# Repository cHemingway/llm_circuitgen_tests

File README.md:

# llm_circuitgen_tests

A benchmark of "circuit as code" tools for LLM-aided circuit design. Every tool
gets the same design brief, and each implementation lives in its own top-level
folder.

Model is Claude Opus 5.5 on Extra thinking level

## Brief

This repository is a benchmark of various "circuit as code" tools for LLM-aided
circuit design. Each tool is given the same prompt, with the tool name and branch
substituted where needed:

> Use `<tool>` to design me a RP2354A powered Solartron 7075 multimeter
> interface, using the 50 way D connector on the Solartron. Put it in the folder
> `<tool>`. Do these changes on a new branch.
>
> DO NOT LOOK AT OTHER BRANCHES FOR CODE, RELY ON THE TOOL, THE DATASHEET, AND
> WHAT YOU CAN FIND ONLINE ONLY, DON'T COPY THE OUTPUTS OF OTHER TOOLS USED IN
> THIS BENCHMARK.
>
> In the top level folder `inputs` is a datasheet for the multimeter. It
> describes how the interface works in section 9.
>
> Signals to/from the multimeter should be opto-isolated to prevent USB ground
> noise from affecting the system. I was thinking therefore they should be done
> through shift registers to minimise the number of signals across the isolation
> barrier.
>
> Select parts from `<tool>`'s library, then LCSC where possible.
>
> Have the board sit flat on the back of the multimeter, using a vertical PCB
> mount D-Sub connector on one side and a vertical USB-B connector on the other
> side of the board.
>
> The board will be rectangular, and mechanically fixed to the solartron using
> the jackscrews on the D-Sub connector, so doesn't need any other mounting
> holes.

When the design work is finished, the session is asked to export the
conversation and add its figures to the Results and Breakdown tables below,
using the prompt in [`EXPORT_PROMPT.md`](EXPORT_PROMPT.md).

## Results

| Tool | Folder | Active time | of which tool time | Total tokens | API calls | API-price estimate | Schematic | PCB prints | Notes |
| --- | --- | --- | --- | --- | --- | --- | --- | --- | --- |
| [tscircuit](https://tscircuit.com) | `tscircuit/` | 3 h 11 min | 2 h 06 min | 156.3 M | 376 | $59.32 | [PDF](tscircuit/outputs/schematic.pdf) | [PDF](tscircuit/outputs/pcb-prints.pdf) | Parts from tscircuit/common, then LCSC. Session log and statistics: [`tscircuit/CONVERSATION.md`](tscircuit/CONVERSATION.md) |
| [atopile](https://atopile.io) | `atopile/` | 1 h 46 min | 38 min | 149.5 M | 370 | $49.34 | [PDF](atopile/schematic/solartron_7075_usb.pdf) | [PDF](atopile/fab/solartron_7075_usb_prints.pdf) | CLI version (`ato`, 0.15.x). This is the last open CLI line and is effectively end-of-life: [PyPI](https://pypi.org/project/atopile/) lists 0.15.9 (12 Sep 2026) as the latest release, and atopile has moved on to [0.16](https://atopile.io/enterprise). Parts from atopile's library, then LCSC. Session log and statistics: [`atopile/CONVERSATION.md`](atopile/CONVERSATION.md) |
| [SKiDL](https://github.com/devbisme/skidl) | `skidl/` | 2 h 29 min | 59 min | 124.5 M | 347 | $46.64 | [PDF](skidl/pcb/render/schematic.pdf) | [PDF](skidl/pcb/print/pcb_prints.pdf) | SKiDL 2.3.0 on KiCad 10 (the brief added "use KiCad 10"). SKiDL has no part library of its own, so parts come from KiCad's libraries, then LCSC. Board built with kinet2pcb and routed with Freerouting 2.5. SKiDL's schematic generator mis-connects nets on this design, so the schematic is drawn by a script and checked against the netlist. Statistics run to the conversation export, and exclude the merge into `main` that came after it. Session log and statistics: [`skidl/CONVERSATION.md`](skidl/CONVERSATION.md) |
| [Manta](https://github.com/Derrick-Derrickson/Manta) | `manta/` | 46 min | – | 62.9 M | 191 | – | [HTML](manta/output/solartron7075.html) | – | Manta 2.0.1 (language revision 2.0). Manta is a schematic and netlist language with no layout, so the result is a checked netlist, a KiCad netlist (with a footprint map and two generated footprints), an LCSC BOM and an HTML schematic. No PCB was made, so there are no prints. Manta's only part library is its `blinky` example; 8 part types came from it, the rest from LCSC. The session transcript kept no cost-state record, so tool time and the price estimate were not recorded; tokens and API calls are summed from the transcript's per-response usage. Statistics run to the conversation export, and exclude the merge into `main` that came after it. Notes on the tool: [`manta/README.md`](manta/README.md#notes-on-the-tool-benchmark-observations). Session log and statistics: [`manta/CONVERSATION.md`](manta/CONVERSATION.md) |
| [Konnect](https://github.com/mixelpixx/Konnect) | `konnect/` | 3 h 33 min | 56 min | 264.4 M | 520 | $112.18 | [PDF](konnect/fab/schematic.pdf) | [PDF](konnect/fab/pcb_layers.pdf) | Konnect 0.13.0, an MCP server that drives KiCad 10.0.6. Parts come from KiCad's libraries, with LCSC numbers. KiCad has no DD-50, so its symbol and footprint were made in the project library. Konnect's Freerouting export refuses KiCad's roundrect pads, so the SMD footprints were copied with rectangular pads. The board was routed with Freerouting 2.4.1 after a pad-rotation bug in Konnect's DSN export was fixed by hand. The ground pours needed hand-placed stitching vias and a small grid router written in the scratchpad. The run stopped twice at a usage limit (12 h 53 min in all, left out of active time) and was compacted once. Tool time and the price estimate are the tool's own counters. The Breakdown prices use the published Opus 5.5 and Haiku 5.5 prices, which reproduce those counters. Statistics run to the conversation export, and exclude the merge into `main` that came after it. Notes on the tool: [`konnect/README.md`](konnect/README.md#notes-on-the-tool). Session log and statistics: [`konnect/CONVERSATION.md`](konnect/CONVERSATION.md) |
| [Fable 5.2 + KiCad](https://www.kicad.org) | `fable_5.2/` | 1 h 18 min | 18 min | 43.9 M | 122 | $46.05 | [PDF](fable_5.2/docs/schematic.pdf) | [PDF](fable_5.2/docs/pcb_top.pdf) | KiCad 10.0.8 (PPA), driven through `kicad-cli` and the `pcbnew` Python module with scripts that write the schematic and board files. Parts come from KiCad's libraries, then LCSC numbers checked against the JLCPCB catalogue. KiCad has no DD-50 plug or TPIC6C595, so those two symbols and the DD-50 and DC-DC footprints were made in the project library. Freerouting could not be run here (executing the downloaded jar was blocked), so the 4-layer board was routed with a grid router written in the project; it has no DRC errors or unconnected pads. The run stopped twice at a usage limit (9 h 06 min in all, left out of active time) and the context was not compacted within the span. Tool time and the price estimate are the tool's own counters. The Breakdown prices use the published per-token prices of the session model, which reproduce those counters. Statistics run to the conversation export, and exclude the merge into `main` that came after it. Notes on the run: [`fable_5.2/README.md`](fable_5.2/README.md#session-statistics). Session log and statistics: [`fable_5.2/CONVERSATION.md`](fable_5.2/CONVERSATION.md) |

Statistics cover the Claude Code session from the first prompt to the merge into
`main`.

- **Active time:** Claude working, including tool runs such as autorouting. It
  excludes time spent waiting for the user.
- **Of which tool time:** the part of the active time spent running tools
  (builds, exports, autorouting, searches) rather than in model calls.
- **Total tokens:** these include prompt-cache reads, which dominate the total
  because every API call re-sends the conversation.
- **API-price estimate:** Claude Code's estimate at API list prices, not a bill.

A dash means the figure was not recorded.

## Breakdown

The Results figures for each tool, split by the kind of work. Every API call in
the session is put in one category according to what it was doing:

- **Schematic & research:** reading the manual, choosing parts and looking them
  up, datasheets and tool documentation, writing the circuit, and netlist and
  schematic work.
- **PCB:** footprints, placement, routing, DRC and other board checks, Gerbers,
  fabrication fixes and PCB prints.
- **Other:** commits, pushes, README writing, status checks and final
  summaries.
- **Not attributable:** calls the session's counters include but the transcript
  doesn't log, such as the `/compact` summary.

How the figures are measured:

- **Tokens:** summed from each call's logged usage.
- **Active time:** each call is credited with the time until the next call,
  including the tool runs it started.
- **API-price estimate:** per-token prices fitted to the session's cost counter
  are applied to each category's tokens.

Calls that did both kinds of work are assigned by their main purpose.

### tscircuit

| | Schematic & research | PCB | Other | Not attributable | Total |
| --- | --- | --- | --- | --- | --- |
| Active time | 1 h 08 min | 1 h 57 min | 4 min | 1 min | 3 h 11 min |
| API calls | 171 | 174 | 31 | – | 376 |
| Total tokens | 61.6 M | 75.2 M | 16.0 M | 3.5 M | 156.3 M |
| Tokens excl. cache reads | 1.33 M | 0.57 M | 0.74 M | 0.74 M | 3.38 M |
| Output tokens | 169 k | 178 k | 26 k | 9 k | 382 k |
| API-price estimate | $24.69 | $21.64 | $9.32 | $3.67 | $59.32 |

### atopile

| | Schematic & research | PCB | Other | Not attributable | Total |
| --- | --- | --- | --- | --- | --- |
| Active time | 1 h 06 min | 31 min | 9 min | 0 min | 1 h 46 min |
| API calls | 226 | 87 | 57 | – | 370 |
| Total tokens | 78.2 M | 42.0 M | 24.7 M | 4.6 M | 149.5 M |
| Tokens excl. cache reads | 0.75 M | 0.32 M | 0.80 M | 0.09 M | 1.97 M |
| Output tokens | 217 k | 104 k | 42 k | 16 k | 378 k |
| API-price estimate | $24.10 | $12.17 | $11.70 | $1.37 | $49.34 |

### SKiDL

| | Schematic & research | PCB | Other | Not attributable | Total |
| --- | --- | --- | --- | --- | --- |
| Active time | 1 h 06 min | 1 h 17 min | 5 min | 1 min | 2 h 29 min |
| API calls | 165 | 158 | 24 | – | 347 |
| Total tokens | 53.3 M | 61.0 M | 9.0 M | 1.1 M | 124.5 M |
| Tokens excl. cache reads | 0.74 M | 0.62 M | 0.69 M | 0.01 M | 2.07 M |
| Output tokens | 238 k | 196 k | 27 k | 9 k | 470 k |
| API-price estimate | $19.31 | $19.39 | $7.51 | $0.43 | $46.64 |

### Konnect

| | Schematic & research | PCB | Other | Not attributable | Total |
| --- | --- | --- | --- | --- | --- |
| Active time | 45 min | 2 h 45 min | 2 min | 1 min | 3 h 33 min |
| API calls | 147 | 364 | 9 | – | 520 |
| Total tokens | 54.5 M | 197.5 M | 7.3 M | 5.1 M | 264.4 M |
| Tokens excl. cache reads | 0.83 M | 3.78 M | 0.84 M | 1.06 M | 6.51 M |
| Output tokens | 235 k | 552 k | 6 k | 17 k | 810 k |
| API-price estimate | $20.17 | $75.58 | $8.12 | $8.32 | $112.18 |

### Fable 5.2 + KiCad

| | Schematic & research | PCB | Other | Not attributable | Total |
| --- | --- | --- | --- | --- | --- |
| Active time | 38 min | 38 min | 2 min | 0 min | 1 h 18 min |
| API calls | 67 | 48 | 7 | – | 122 |
| Total tokens | 16.5 M | 23.5 M | 3.9 M | 0 | 43.9 M |
| Tokens excl. cache reads | 0.54 M | 0.33 M | 0.96 M | 0 | 1.82 M |
| Output tokens | 198 k | 145 k | 9 k | 0 | 352 k |
| API-price estimate | $16.63 | $13.32 | $16.09 | $0.00 | $46.05 |

## Review feedback

After the design is finished, each tool's session gets the same review comments,
in this order:

> 1. Can you tidy up the routing through pin swapping the shift registers /
>    resistor arrays?
> 2. Did you try swapping pins between parts as well or just within the same
>    part?
> 3. Try moving parts too

Statistics are measured as above, from the first review comment to the last
reply.

When the review is finished, the session is asked to export the review log and
fill in its row below, using the prompt in
[`REVIEW_EXPORT_PROMPT.md`](REVIEW_EXPORT_PROMPT.md).

| Tool | Active time | of which tool time | Total tokens | API calls | API-price estimate | Notes |
| --- | --- | --- | --- | --- | --- | --- |
| [tscircuit](https://tscircuit.com) | 1 h 35 min | 1 h 12 min | 48.9 M | 97 | $16.38 | Review log and statistics: [`tscircuit/REVIEW_CONVERSATION.md`](tscircuit/REVIEW_CONVERSATION.md) |
| [atopile](https://atopile.io) | 2 h 28 min | 2 h 03 min | 53.1 M | 141 | $16.94 | Review log and statistics: [`atopile/REVIEW_CONVERSATION.md`](atopile/REVIEW_CONVERSATION.md) |
| [SKiDL](https://github.com/devbisme/skidl) | 38 min | 21 min | 34.1 M | 65 | $9.80 | Turn 1 from Claude Code's counters. No counter record was written after turns 2–3, so their tokens come from the transcript, their tool time from tool-call timestamps and their price from per-token prices fitted to the session's cost snapshots. Review log and statistics: [`skidl/REVIEW_CONVERSATION.md`](skidl/REVIEW_CONVERSATION.md) |
| [Manta](https://github.com/Derrick-Derrickson/Manta) | – | – | – | – | – | |
| [Konnect](https://github.com/mixelpixx/Konnect) | 2 h 35 min | 49 min | 226.6 M | 413 | $86.47 | The resumed session wrote no cost-state counters, so every figure comes from the transcript. Tokens and API calls are summed from the per-response usage. Tool time is each tool call's request-to-result time, which reads about 4 % high. The price uses the published Opus 5.5 prices. Active time leaves out a 26 min wait for the user's answer, two usage-limit stops, and about an hour when the API could not be reached. Review log and statistics: [`konnect/REVIEW_CONVERSATION.md`](konnect/REVIEW_CONVERSATION.md) |
| [Fable 5.2 + KiCad](https://www.kicad.org) | – | – | – | – | – | |

## Layout

| Folder | Contents |
| --- | --- |
| `inputs/` | Source material: OCR'd Solartron 7075 service manual (interface in Section 9) |
| `tscircuit/` | [tscircuit](https://tscircuit.com) implementation; see its README |
| `atopile/` | [atopile](https://atopile.io) (CLI) implementation; see its README |
| `skidl/` | [SKiDL](https://github.com/devbisme/skidl) implementation, with a KiCad 10 board; see its README |
| `manta/` | [Manta](https://github.com/Derrick-Derrickson/Manta) implementation, schematic and netlist only (no board); see its README |
| `konnect/` | [Konnect](https://github.com/mixelpixx/Konnect) (MCP server for KiCad) implementation, with a KiCad 10 board; see its README |
| `fable_5.2/` | [KiCad](https://www.kicad.org) 10 implementation (`kicad-cli` and `pcbnew` scripts), with a 4-layer board; see its README |

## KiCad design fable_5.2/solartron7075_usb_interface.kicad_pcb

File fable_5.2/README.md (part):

# Solartron 7075 opto-isolated USB interface (RP2354A)

KiCad 10 project for a small board that plugs straight onto the 50-way D
connector of a Solartron 7075 DVM and gives full remote control / read-out over
USB.  An RP2354A talks to the multimeter through shift registers; only six
signals cross the isolation barrier, all through optocouplers.

| | |
|---|---|
| Schematic | `solartron7075_usb_interface.kicad_sch` (+ 4 sub-sheets), PDF in `docs/schematic.pdf` |
| PCB | `solartron7075_usb_interface.kicad_pcb`, 116 x 50 mm, 4 layers, 1.6 mm |
| Fabrication | `production/` (gerbers + drill zip, JLCPCB BOM / CPL, DRC and ERC reports) |
| Plots / renders | `docs/` |
| Generators | `scripts/` (the whole project is regenerated by `scripts/build.sh`) |

## What it connects to (please read)

Section 9 of the service manual documents the **70754 Parallel BCD Interface
Unit** and gives the pin-out of its 50-way "Systems Interface" socket **SKB**
(page 9.9).  This board is designed for that connector: J1 pin numbers are SKB
pin numbers and the logic levels are those of page 9.1.

It is *not* designed for the bare DVM rear socket SK1 (the one the 70754 plugs
into).  SK1 carries a different, multiplexed word-serial bus that the manual
only shows on the 70754 circuit diagrams, so a 7075 without the 70754 unit
would need a different board.

## How it works

```
USB-B -> RP2354A -> 74LVC125 -> 3 x HCPL-2631 -> 2 x TPIC6C595 (16 open-drain outputs)  -> SKB 38..50
                                 (6 channels)  <- 5 x 74HCT165  (40 inputs, 100k series) <- SKB 1..36, 38
USB 5 V -> ferrite -> B0509S isolated DC-DC (9 V) -> L78M05 -> +5V_ISO
```

Signals across the barrier:

<!-- GPIO:BEGIN (generated by scripts/export.py) -->
| Signal | RP2354A | Optocoupler | Direction | Function |
|---|---|---|---|---|
| SCK | GPIO2 (SPI0 SCK) | U5 channel 1 | to DVM side | shift clock for both chains, rising edge shifts |
| MOSI | GPIO3 (SPI0 TX) | U6 channel 2 | to DVM side | command bits into the TPIC6C595 chain |
| MISO | GPIO4 (SPI0 RX) | U7 channel 1 | to MCU | data out of the 74HCT165 chain |
| LATCH | GPIO0 | U5 channel 2 | to DVM side | low = load the 40 inputs; rising edge = copy command word to the outputs |
| OEn | GPIO1 | U6 channel 1 | to DVM side | low = command outputs enabled |
| DRDY | GPIO11 | U7 channel 2 | to MCU | PRINT command level (SKB 34): high = reading complete |

Other pins: GPIO8 / GPIO5 = UART1 TX / RX on test pads TP1 / TP2, GPIO25 =
activity LED, SWD on J3 (Raspberry Pi 3-pin debug connector), BOOTSEL and RESET
buttons.
<!-- GPIO:END -->

All six channels are non-inverting end to end and "LED off" is the high level.
While the MCU is in reset or unprogrammed (pull-ups RN1), or USB is unplugged,
OEn is high and every command line is released, so the multimeter behaves
exactly as if nothing were plugged into SKB (front panel stays usable).

### Transfer

1. Pulse LATCH low (>= 1 us).  The falling edge loads SKB pins into the
   74HCT165s; the rising edge copies the last 16 bits previously shifted into
   the TPIC6C595s to the outputs.
2. Clock 40 bits, SPI mode 3 (or 0), <= 1 MHz: send 24 padding bits followed
   by the 16-bit command word MSB first, and read 40 status bits.
3. Pulse LATCH again (or simply start the next transfer) to apply the command.
4. Drive OEn low once the first command word has been latched.

Which register input reads which SKB pin, and which driver output drives which
command line, was chosen by `scripts/optimise.py` for the shortest layout (see
"Pin assignment and placement" below), so the bit order is not the pin order.
The tables are generated from `scripts/pinmap.json`; `docs/skb_bits.h` has the
same numbers as C macros.

<!-- BITMAP:BEGIN (generated by scripts/export.py) -->
**Status stream** (40 bits, bit 0 is shifted out first):

| Bit | Register input | SKB pin | Signal |
|---|---|---|---|
| 0 | U10 D7 | 2 | 8 x 10^5 |
| 1 | U10 D6 | 18 | 8 x 10^1 |
| 2 | U10 D5 | 35 | DATA CAN CHANGE |
| 3 | U10 D4 | 36 | OVERLOAD |
| 4 | U10 D3 | 34 | PRINT level |
| 5 | U10 D2 | 1 | 1 x 10^6 |
| 6 | U10 D1 | 3 | 4 x 10^5 |
| 7 | U10 D0 | 19 | 4 x 10^1 |
| 8 | U11 D7 | 22 | 8 x 10^0 |
| 9 | U11 D6 | 38 | FRONT PANEL LOCKOUT (read-back) |
| 10 | U11 D5 | 5 | 1 x 10^5 |
| 11 | U11 D4 | 20 | 2 x 10^1 |
| 12 | U11 D3 | 21 | 1 x 10^1 |
| 13 | U11 D2 | 4 | 2 x 10^5 |
| 14 | U11 D1 | 6 | 8 x 10^4 |
| 15 | U11 D0 | 23 | 4 x 10^0 |
| 16 | U12 D7 | 26 | polarity + |
| 17 | U12 D6 | 27 | polarity - |
| 18 | U12 D5 | 24 | 2 x 10^0 |
| 19 | U12 D4 | 25 | 1 x 10^0 |
| 20 | U12 D3 | 7 | 4 x 10^4 |
| 21 | U12 D2 | 8 | 2 x 10^4 |
| 22 | U12 D1 | 9 | 1 x 10^4 |
| 23 | U12 D0 | 10 | 8 x 10^3 |
| 24 | U13 D7 | 14 | 8 x 10^2 |
| 25 | U13 D6 | 31 | range out (2) |
| 26 | U13 D5 | 29 | function out |
| 27 | U13 D4 | 28 | function out |
| 28 | U13 D3 | 12 | 2 x 10^3 |
| 29 | U13 D2 | 11 | 4 x 10^3 |
| 30 | U13 D1 | 13 | 1 x 10^3 |
| 31 | U13 D0 | 30 | range out (4) |
| 32 | U14 D7 | - | hard-wired 1 |
| 33 | U14 D6 | - | hard-wired 0 |
| 34 | U14 D5 | - | hard-wired 0 |
| 35 | U14 D4 | 33 | PRINT pulse |
| 36 | U14 D3 | 16 | 2 x 10^2 |
| 37 | U14 D2 | 32 | range out (1) |
| 38 | U14 D1 | 17 | 1 x 10^2 |
| 39 | U14 D0 | 15 | 4 x 10^2 |

**Command word** (16 bits, sent MSB first, so bit 15 goes out first):

| Bit | Register output | SKB pin | Signal |
|---|---|---|---|
| 0 | U15 DRAIN0 | 38 | FRONT PANEL LOCKOUT |
| 1 | U15 DRAIN1 | 40 | SAMPLE pulse (via Q1) |
| 2 | U15 DRAIN2 | 39 | SAMPLE (contact to 0 V) |
| 3 | U15 DRAIN3 | 42 | FUNCTION |
| 4 | U15 DRAIN4 | 43 | FUNCTION |
| 5 | U15 DRAIN5 | 41 | RATIO |
| 6 | U15 DRAIN6 | 44 | INTEGRATION TIME (4) |
| 7 | U15 DRAIN7 | 45 | INTEGRATION TIME (2) |
| 8 | U16 DRAIN0 | - | spare |
| 9 | U16 DRAIN1 | 47 | AUTORANGE |
| 10 | U16 DRAIN2 | 46 | INTEGRATION TIME (1) |
| 11 | U16 DRAIN3 | 48 | RANGE (1) |
| 12 | U16 DRAIN4 | 49 | RANGE (2) |
| 13 | U16 DRAIN5 | 50 | RANGE (4) |
| 14 | U16 DRAIN6 | - | spare |
| 15 | U16 DRAIN7 | - | spare |
<!-- BITMAP:END -->

Status bits follow the level on the SKB pin.  The read-back of SKB 38 (FRONT
PANEL LOCKOUT) is pulled up by the multimeter, so with that output released a 1
means "DVM connected and powered".  The three hard-wired bits check that the
isolated supply and the whole chain are alive.

In the command word a 1 switches the open-drain output on, i.e. puts logic 0
on the line.  SKB 40 is the exception: a 1 drives it *high* through Q1 (the
manual asks for a positive pulse of 3..8 V, > 100 us).

In REP (free-running) mode the 70754 holds both PRINT outputs low and its
output shift registers ripple while a new reading is transferred, so firmware
should read twice and compare; in single-sample mode use DRDY.

## Design notes

* **Isolation.**  HCPL-2631 dual 10 MBd optocouplers (gull-wing SMD-8) straddle
  a 6.8 mm copper-free strip on all four layers.  The only narrower point is
  between pins 2 and 3 of the SIP-4 DC-DC converter (1.0 mm copper gap, part
  rated 1.5 kV); the project footprint for PS1 uses narrower pads than KiCad's
  stock SIP-4 footprint (0.29 mm gap).  This is functional isolation to break
  the USB ground loop, not a safety barrier.  A custom DRC rule
  (`.kicad_dru`) enforces >= 1 mm between the two domains.
* **Isolated supply.**  SKB has no supply pin, so the DVM-side logic is powered
  from USB through a 1 W isolated converter.  A 9 V converter followed by a
  linear L78M05 is used instead of an unregulated 5 V -> 5 V module, whose
  output would exceed 5.5 V at this light load.  Load is about 65 mA.
* **Inputs.**  The 70754 drives SKB from 7404 TTL outputs, hence 74HCT165 (TTL
  thresholds).  Each line has 100k in series and 100k to GND_ISO: at most
  ~35 uA per pin flows into the unpowered board, and the inputs are defined
  when the board is not plugged in.
* **Outputs.**  TPIC6C595 open-drain shift registers sink the multimeter's own
  4.7k pull-ups (the 70754 inputs are TTL with pull-ups to +5 V) and are
  high-impedance without power.
* **RP2354A.**  Raspberry Pi reference circuit: 12 MHz ABM8-272-T3 crystal,
  polarised AOTA-B201610S3R3 inductor with the VIN/output capacitors stacked
  above pins 47-49 and the switch node routed between their pads as in the
  reference layout.  DVDD pins 6/23 and VREG_FB reach +1V1 through vias under
  the package.
* **Mechanics.**  J1 (DD-50 plug, straight PCB pins, plain 3.1 mm flange holes)
  is the only part on the bottom side; everything else, including the vertical
  USB-B socket, is on the top side.  The board is held by two 4-40 UNC screws
  that pass through the 3.2 mm plated holes (61.11 mm apart) and J1's flange
  into the jackposts of SKB.  The screw-head pads are 6.4 mm and tied to
  GND_ISO through R24 (0R, remove to float the shell).  Screws of about 16 mm
  (5/8") are needed; 5 mm spacers between PCB and flange stop the board
  bending when they are tightened.  Seen from the top with J1's row 1..17
  uppermost, pin 1 is top right and the USB end is on the right.
* **Pin assignment and placement.**  On the multimeter side almost every
  connection is exchangeable: any 74HCT165 input can read any SKB pin, any
  resistor of any 100k array can be its series or pull-down resistor, any
  TPIC6C595 output can drive any command line, and the registers can sit in the
  chains in any order.  `scripts/optimise.py` solves that assignment exactly for
  a given placement (three minimum-length matchings plus the chain order, so
  pins are swapped within and between parts) and compares placements by routing
  each one completely.  Results, all with clean DRC:

  | Variant | Vias | Track | of which vias on SKB lines / register control |
  |---|---|---|---|
  | original placement, bit n = pin n+1 | 328 | 2.70 m | 84 / 50 |
  | original placement, pins swapped | 275 | 2.05 m | 48 / 31 |
  | parts moved, pull-downs below the connector | 241 | 2.28 m | 34 / 13 |
  | parts moved, pull-downs above the connector | 244 | 1.94 m | 32 / 17 |
  | + MCU side: GPIOs, buffer gates, opto channels swapped | 241 | 1.88 m | 32 / 17 |
  | + MCU side: buffer, pull-up array and test pads moved (used) | 236 | 1.86 m | 32 / 17 |

  The router's result varies by a few vias from run to run; the board in this
  folder has 234 vias and 1.86 m of track (first revision: 330 and 2.66 m).
  About 160 of the vias are plane connections of supply pins, which swapping
  cannot remove.  In the layout used, the five registers sit in one row above
  the connector, turned so that each is as wide as the eight pins it reads,
  with one series array on each side of the chip.  The pull-down arrays stand
  upright above every second pin of the top row: that pin's track runs under
  the array body, the neighbouring lines tee into the pads on their side.
  Twelve fine-tuning variants of the placement all landed within 237..246
  vias, so the floorplan matters and its exact dimensions do not.

  On the MCU side the GPIO of each signal (SCK / MOSI / MISO kept on pins of
  one hardware SPI block, the test pads on a UART pair), the 74LVC125 gate
  that buffers it, its pull-up resistor in RN1, the optocoupler channel that
  carries it and the 74AHCT125 gates of the uplink are assigned the same way,
  by estimated length plus a penalty per crossing.  That side gains much less
  (34 -> 25 vias on its nets): only about a dozen of its vias belong to
  exchangeable connections, the rest are USB, crystal, QSPI, reset and core
  supply.  Swapping alone bought four vias; turning U4 and RN1 round, so that
  the GPIO lines meet the pull-ups first and the buffer outputs face the
  optocouplers, and moving the test pads bought the rest.  Putting RN1 in line
  right at the MCU pins, or letting signals use the GPIOs on the crystal / SWD
  side of the package, routed worse or left a connection unrouted.
* **Layers.**  F.Cu / B.Cu signals, In1 split ground plane (GND_ISO | GND),
  In2 split supply plane (+5V_ISO | +3V3).  Rules: 0.2 mm tracks, 0.15 mm
  clearance, 0.6 / 0.3 mm vias (0.15 mm / 0.12 mm only for the regulator switch
  node).

## Parts

Symbols and footprints come from KiCad's own libraries wherever they exist;
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
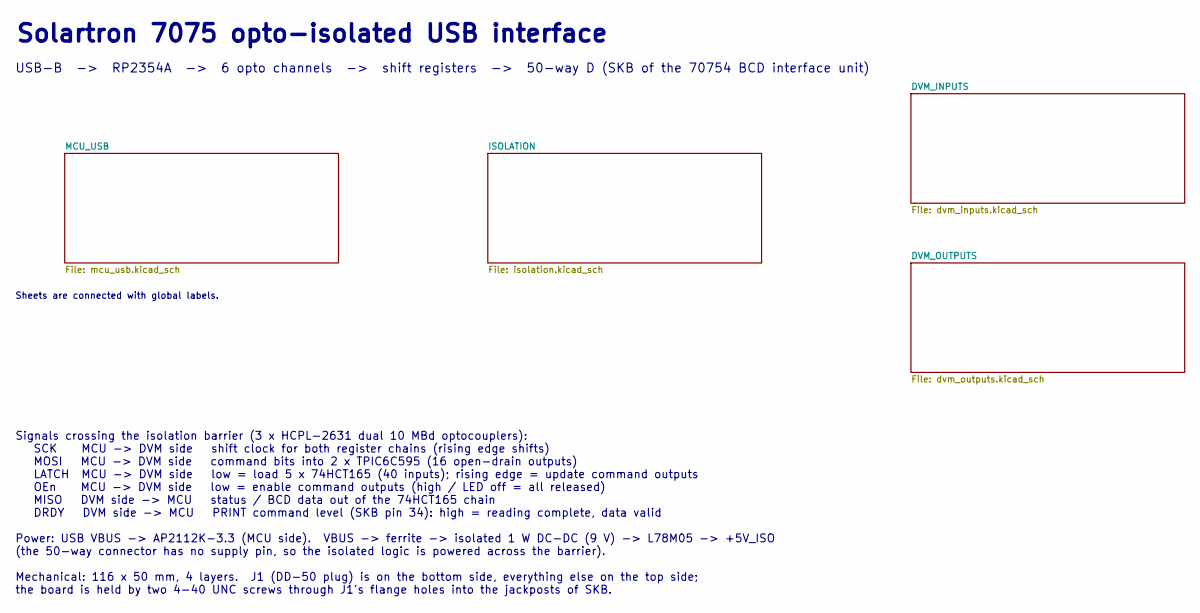
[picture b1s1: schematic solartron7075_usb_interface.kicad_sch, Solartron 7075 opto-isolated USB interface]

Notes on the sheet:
USB-B -> RP2354A -> 6 opto channels -> shift registers -> 50-way D (SKB of the 70754 BCD interface unit)
Sheets are connected with global labels.
Solartron 7075 opto-isolated USB interface
Signals crossing the isolation barrier (3 x HCPL-2631 dual 10 MBd optocouplers): SCK MCU -> DVM side shift clock for both register chains (rising edge shifts) MOSI MCU -> DVM side command bits into 2 x TPIC6C595 (16 open-drain outputs) LATCH MCU -> DVM side low = load 5 x 74HCT165 (40 inputs); risi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

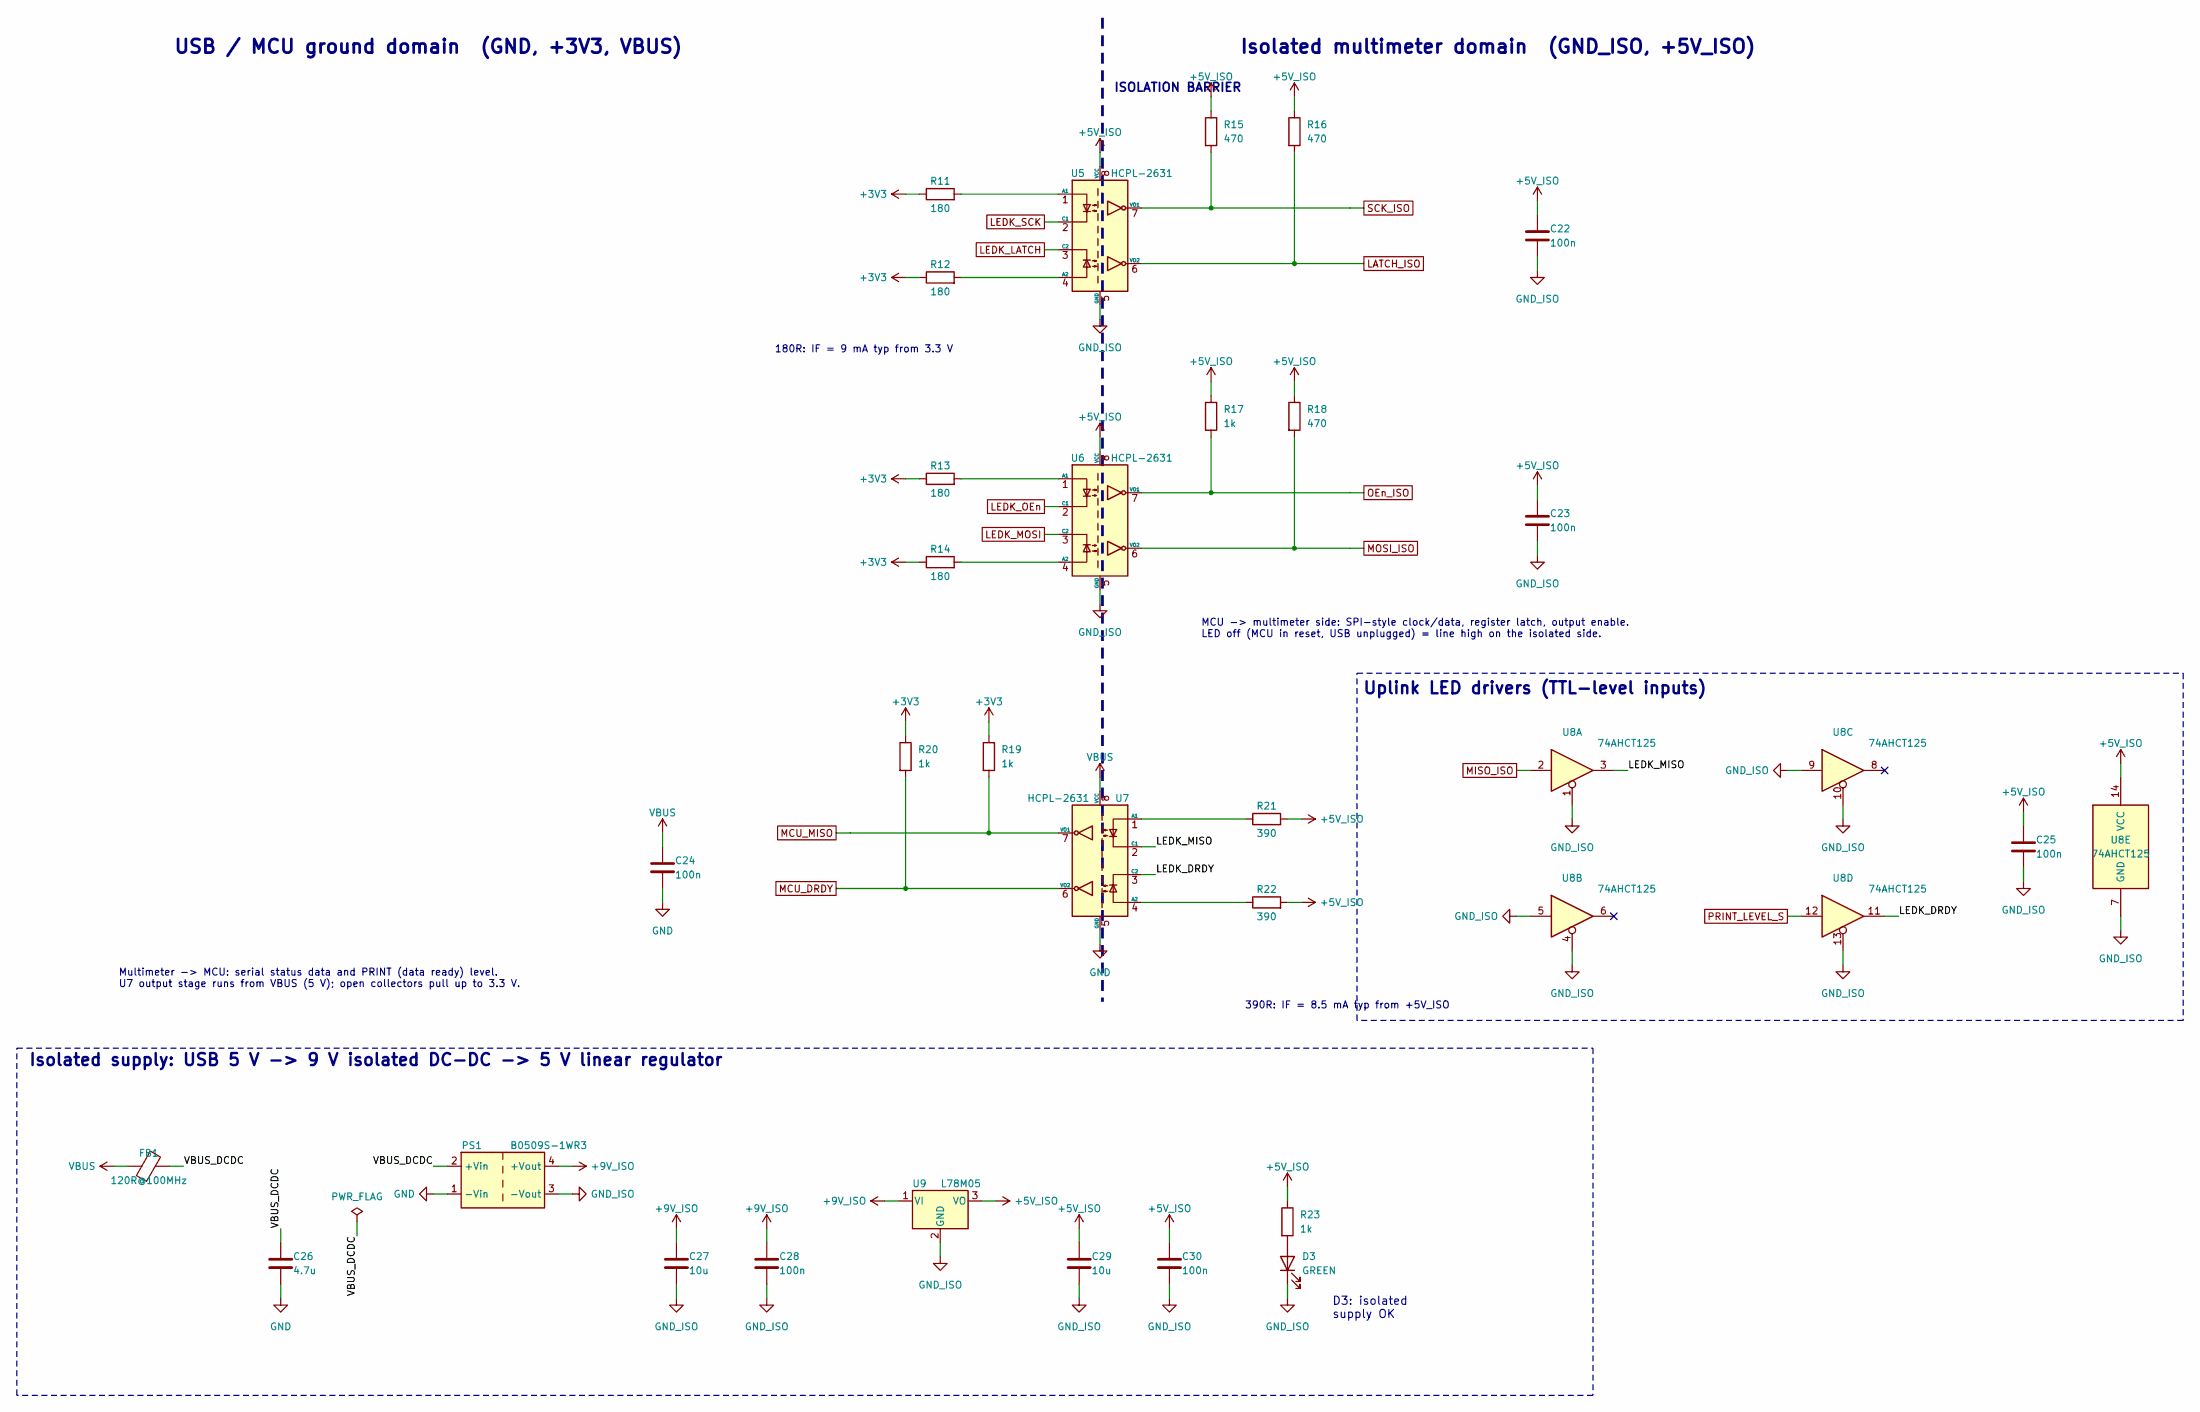
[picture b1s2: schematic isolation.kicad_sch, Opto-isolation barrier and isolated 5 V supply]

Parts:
C22, C23, C24, C25, C28, C30: 100n; C_0603_1608Metric; MPN CC0603KRX7R9BB104; LCSC C14663
C26: 4.7u; C_0603_1608Metric; MPN CL10A475KO8NNNC; LCSC C19666
C27, C29: 10u; C_0805_2012Metric; MPN CL21A106KAYNNNE; LCSC C15850
D3: GREEN; LED_0603_1608Metric; MPN KT-0603G; LCSC C12624
FB1: 120R@100MHz; L_0603_1608Metric; MPN BLM18PG121SN1D; LCSC C14709
PS1: B0509S-1WR3; Converter_DCDC_Mornsun_B05xxS-1WR3_SIP4_THT; MPN B0509S-1WR3; LCSC C5369463
R11, R12, R13, R14: 180; R_0603_1608Metric; MPN 0603WAF1800T5E; LCSC C22828
R15, R16, R18: 470; R_0603_1608Metric; MPN 0603WAF4700T5E; LCSC C23179
R17, R19, R20, R23: 1k; R_0603_1608Metric; MPN 0603WAF1001T5E; LCSC C21190
R21, R22: 390; R_0603_1608Metric; MPN 0603WAF3900T5E; LCSC C23151
U5, U6, U7: HCPL-2631; SMDIP-8_W9.53mm; MPN HCPL-2631-500E; LCSC C188742
U8: 74AHCT125; SOIC-14_3.9x8.7mm_P1.27mm; MPN SN74AHCT125DR; LCSC C155176
U9: L78M05; TO-252-2; MPN L78M05ABDT-TR; LCSC C58069

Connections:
+3V3: R11.1, R12.1, R13.1, R14.1, R19.1, R20.1; also elsewhere on the board
+5V_ISO: C22.1, C23.1, C25.1, C29.1, C30.1, R15.1, R16.1, R17.1, R18.1, R21.2, R22.2, R23.1, U5.8 (VCC), U6.8 (VCC), U8.14 (VCC), U9.3 (VO); also elsewhere on the board
+9V_ISO: C27.1, C28.1, PS1.4 (+Vout), U9.1 (VI)
/ISOLATION/LEDK_DRDY: U7.3 (C2), U8.11
/ISOLATION/LEDK_MISO: U7.2 (C1), U8.3
/ISOLATION/VBUS_DCDC: C26.1, FB1.2, PS1.2 (+Vin)
GND: C24.2, C26.2, PS1.1 (-Vin), U7.5 (GND); also elsewhere on the board
GND_ISO: C22.2, C23.2, C25.2, C27.2, C28.2, C29.2, C30.2, D3.1 (K), PS1.3 (-Vout), U5.5 (GND), U6.5 (GND), U8.1, U8.4, U8.5, U8.7 (GND), U8.9, U8.10, U8.13, U9.2 (GND); also elsewhere on the board
LATCH_ISO: R16.2, U5.6 (VO2); also elsewhere on the board
LEDK_LATCH: U5.3 (C2); also elsewhere on the board
LEDK_MOSI: U6.3 (C2); also elsewhere on the board
LEDK_OEn: U6.2 (C1); also elsewhere on the board
LEDK_SCK: U5.2 (C1); also elsewhere on the board
MCU_DRDY: R20.2, U7.6 (VO2); also elsewhere on the board
MCU_MISO: R19.2, U7.7 (VO1); also elsewhere on the board
MISO_ISO: U8.2; also elsewhere on the board
MOSI_ISO: R18.2, U6.6 (VO2); also elsewhere on the board
unnamed: D3.2 (A), R23.2
unnamed: R11.2, U5.1 (A1)
unnamed: R12.2, U5.4 (A2)
unnamed: R13.2, U6.1 (A1)
unnamed: R14.2, U6.4 (A2)
unnamed: R21.1, U7.1 (A1)
unnamed: R22.1, U7.4 (A2)
OEn_ISO: R17.2, U6.7 (VO1); also elsewhere on the board
PRINT_LEVEL_S: U8.12; also elsewhere on the board
SCK_ISO: R15.2, U5.7 (VO1); also elsewhere on the board
VBUS: C24.1, FB1.1, U7.8 (VCC); also elsewhere on the board

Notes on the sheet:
180R: IF = 9 mA typ from 3.3 V
Isolated multimeter domain (GND_ISO, +5V_ISO)
USB / MCU ground domain (GND, +3V3, VBUS)
ISOLATION BARRIER
Uplink LED drivers (TTL-level inputs)
Isolated supply: USB 5 V -> 9 V isolated DC-DC -> 5 V linear regulator
390R: IF = 8.5 mA typ from +5V_ISO
Multimeter -> MCU: serial status data and PRINT (data ready) level. U7 output stage runs from VBUS (5 V); open collectors pull up to 3.3 V.
MCU -> multimeter side: SPI-style clock/data, register latch, output enable. LED off (MCU in reset, USB unplugged) = line high on the isolated side.
D3: isolated supply OK

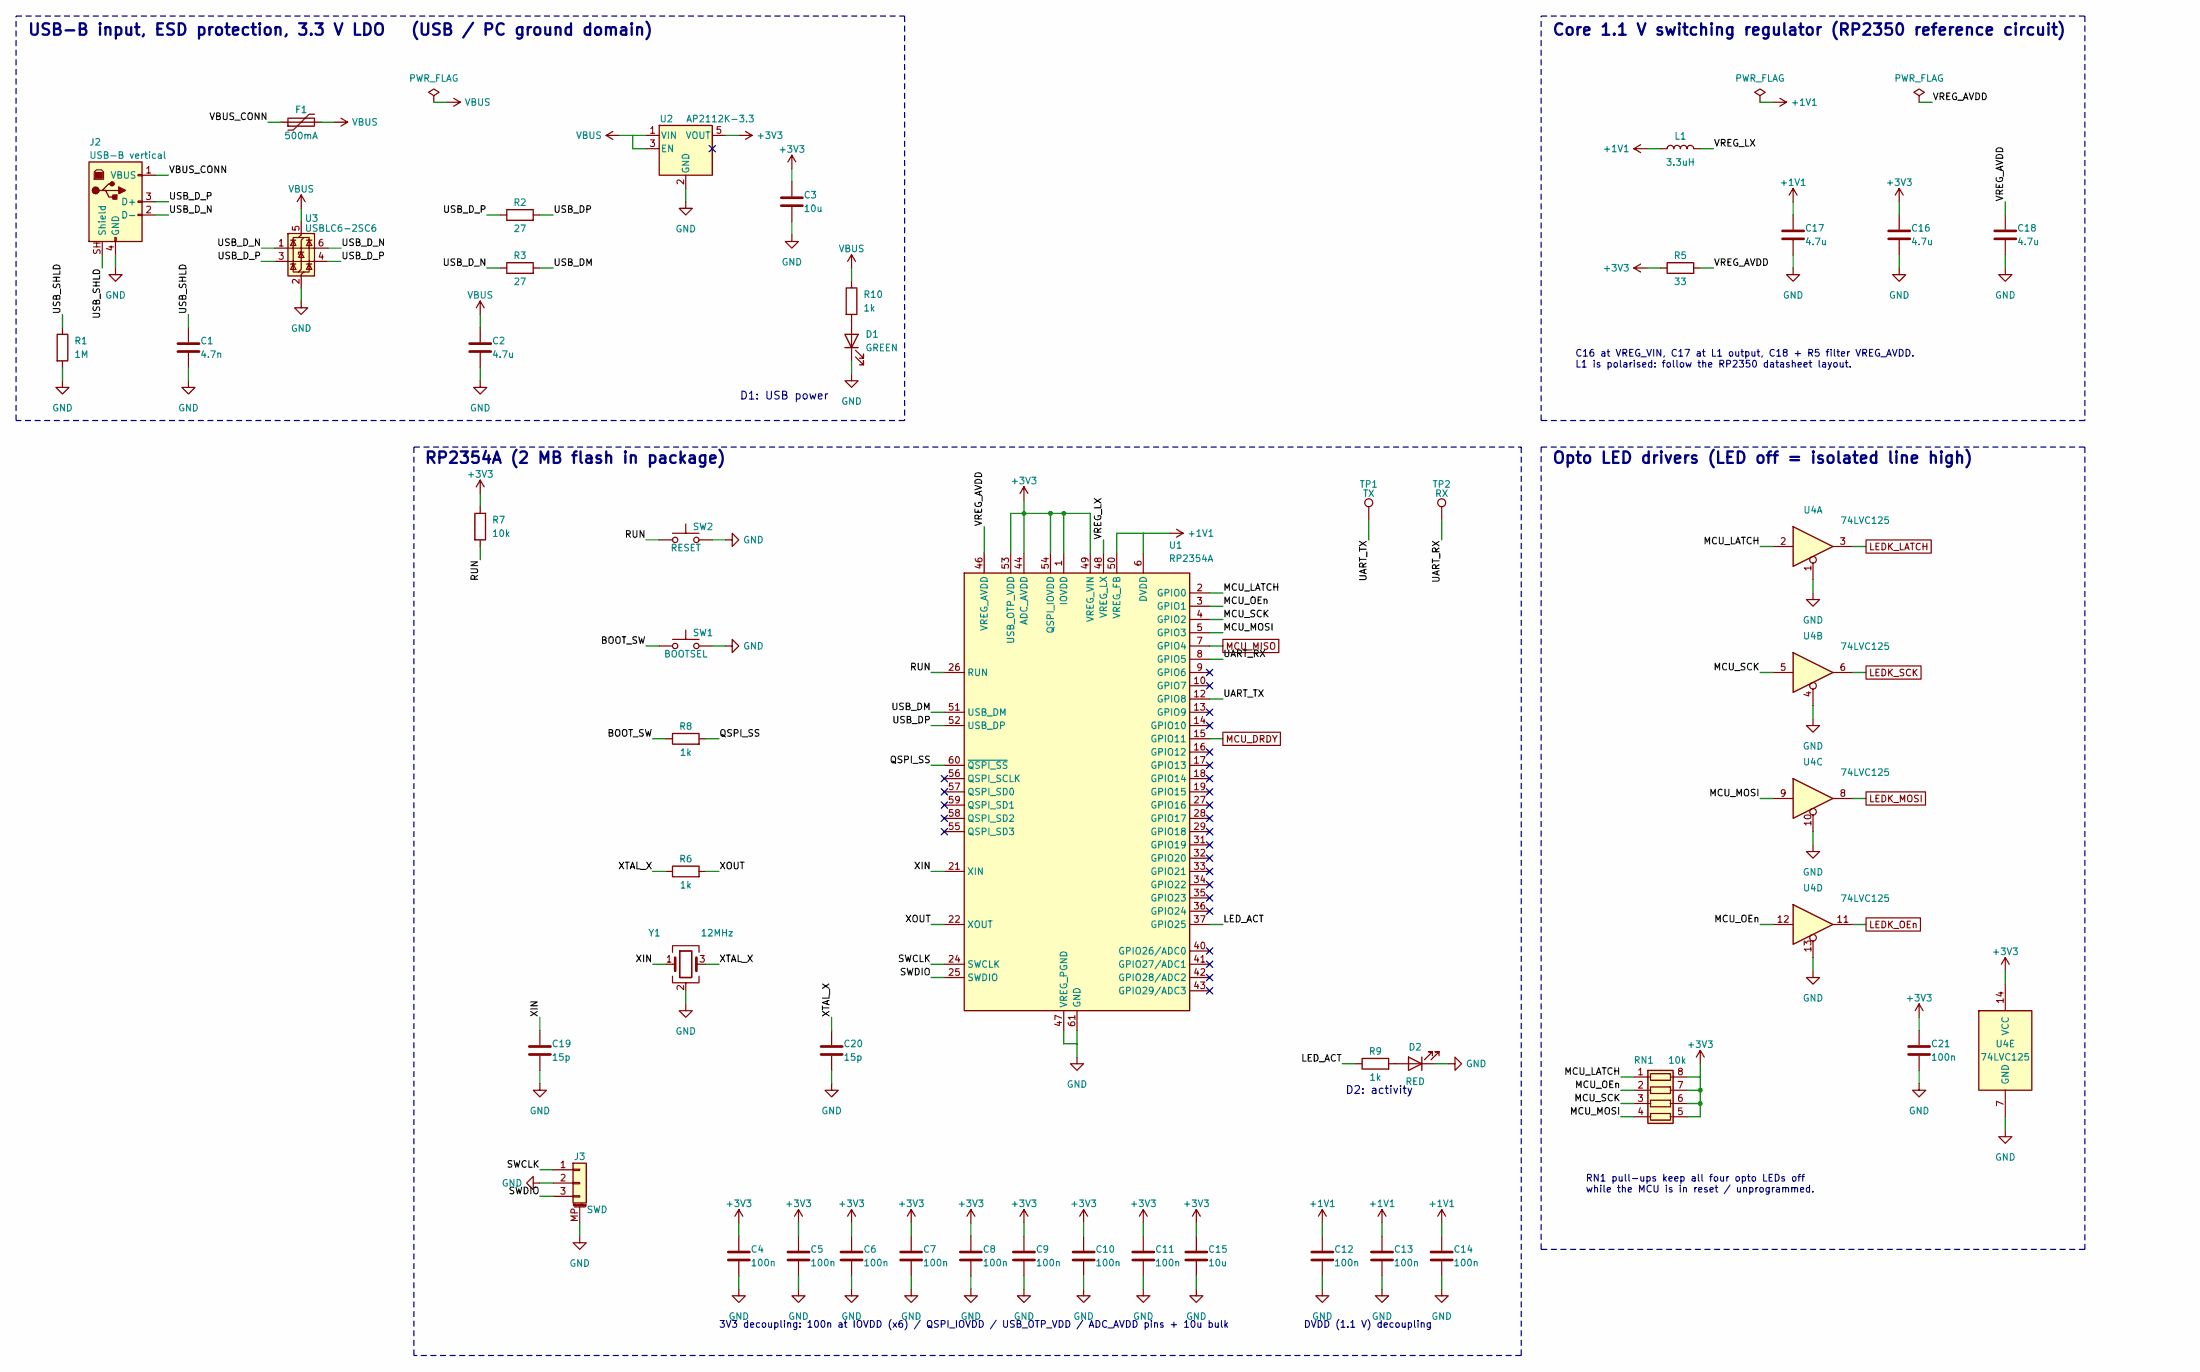
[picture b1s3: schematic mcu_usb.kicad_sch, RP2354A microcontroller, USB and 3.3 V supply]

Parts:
C1: 4.7n; C_0603_1608Metric; MPN CC0603KRX7R9BB472; LCSC C106218
C2: 4.7u; C_0603_1608Metric; MPN CL10A475KO8NNNC; LCSC C19666
C3, C15: 10u; C_0603_1608Metric; MPN CL10A106KP8NNNC; LCSC C19702
C4, C5, C6, C7, C8, C9, C10, C11, C12, C13, C14, C21: 100n; C_0402_1005Metric; MPN CL05B104KO5NNNC; LCSC C1525
C16, C17, C18: 4.7u; C_0402_1005Metric; MPN CL05A475MP5NRNC; LCSC C23733
C19, C20: 15p; C_0402_1005Metric; MPN 0402CG150J500NT; LCSC C1548
D1: GREEN; LED_0603_1608Metric; MPN KT-0603G; LCSC C12624
D2: RED; LED_0603_1608Metric; MPN KT-0603R; LCSC C2286
F1: 500mA; Fuse_1206_3216Metric; MPN nSMD050-16V; LCSC C70075
J2: USB-B vertical; USB_B_TE_5787834_Vertical; MPN 5787834-1; LCSC C592900
J3: SWD; JST_SH_SM03B-SRSS-TB_1x03-1MP_P1.00mm_Horizontal; MPN SM03B-SRSS-TB(LF)(SN); LCSC C160403
L1: 3.3uH; L_Abracon_AOTA-B201610S; MPN AOTA-B201610S3R3-101-T; LCSC C42411119
R1: 1M; R_0603_1608Metric; MPN 0603WAF1004T5E; LCSC C22935
R2, R3: 27; R_0402_1005Metric; MPN 0402WGF270JTCE; LCSC C25100
R5: 33; R_0402_1005Metric; MPN 0402WGF330JTCE; LCSC C25105
R6, R8: 1k; R_0402_1005Metric; MPN 0402WGF1001TCE; LCSC C11702
R7: 10k; R_0402_1005Metric; MPN 0402WGF1002TCE; LCSC C25744
R9, R10: 1k; R_0603_1608Metric; MPN 0603WAF1001T5E; LCSC C21190
RN1: 10k; R_Array_Convex_4x0603; MPN 4D03WGJ0103T5E; LCSC C29718
SW1: BOOTSEL; SW_Push_1P1T_XKB_TS-1187A; MPN TS-1187A-B-A-B; LCSC C318884
SW2: RESET; SW_Push_1P1T_XKB_TS-1187A; MPN TS-1187A-B-A-B; LCSC C318884
TP1: TX; TestPoint_Pad_D1.0mm
TP2: RX; TestPoint_Pad_D1.0mm
U1: RP2354A; QFN-60-1EP_7x7mm_P0.4mm_EP3.4x3.4mm; MPN RP2354A; LCSC C41378174
U2: AP2112K-3.3; SOT-23-5; MPN AP2112K-3.3TRG1; LCSC C51118
U3: USBLC6-2SC6; SOT-23-6; MPN USBLC6-2SC6; LCSC C7519
U4: 74LVC125; TSSOP-14_4.4x5mm_P0.65mm; MPN SN74LVC125APWR; LCSC C7813
Y1: 12MHz; Crystal_SMD_3225-4Pin_3.2x2.5mm; MPN ABM8-272-T3; LCSC C20625731

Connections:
+1V1: C12.1, C13.1, C14.1, C17.1, L1.1, U1.6 (DVDD), U1.23 (DVDD), U1.39 (DVDD), U1.50 (VREG_FB)
+3V3: C3.1, C4.1, C5.1, C6.1, C7.1, C8.1, C9.1, C10.1, C11.1, C15.1, C16.1, C21.1, R5.1, R7.1, RN1.5 (R4.2), RN1.6 (R3.2), RN1.7 (R2.2), RN1.8 (R1.2), U1.1 (IOVDD), U1.11 (IOVDD), U1.20 (IOVDD), U1.30 (IOVDD), U1.38 (IOVDD), U1.44 (ADC_AVDD), U1.45 (IOVDD), U1.49 (VREG_VIN), U1.53 (USB_OTP_VDD), U1.54 (QSPI_IOVDD), U2.5 (VOUT), U4.14 (VCC); also elsewhere on the board
/MCU_USB/BOOT_SW: R8.1, SW1.1
/MCU_USB/LED_ACT: R9.1, U1.37 (GPIO25)
/MCU_USB/MCU_LATCH: RN1.1 (R1.1), U1.2 (GPIO0), U4.2
/MCU_USB/MCU_MOSI: RN1.4 (R4.1), U1.5 (GPIO3), U4.9
/MCU_USB/MCU_OEn: RN1.2 (R2.1), U1.3 (GPIO1), U4.12
/MCU_USB/MCU_SCK: RN1.3 (R3.1), U1.4 (GPIO2), U4.5
/MCU_USB/QSPI_SS: R8.2, U1.60 (~QSPI_SS)
/MCU_USB/RUN: R7.2, SW2.1, U1.26 (RUN)
/MCU_USB/SWCLK: J3.1, U1.24 (SWCLK)
/MCU_USB/SWDIO: J3.3, U1.25 (SWDIO)
/MCU_USB/UART_RX: TP2.1, U1.8 (GPIO5)
/MCU_USB/UART_TX: TP1.1, U1.12 (GPIO8)
/MCU_USB/USB_DM: R3.2, U1.51 (USB_DM)
/MCU_USB/USB_DP: R2.2, U1.52 (USB_DP)
/MCU_USB/USB_D_N: J2.2 (D-), R3.1, U3.1 (I/O1), U3.6 (I/O1)
/MCU_USB/USB_D_P: J2.3 (D+), R2.1, U3.3 (I/O2), U3.4 (I/O2)
/MCU_USB/USB_SHLD: C1.1, J2.SH (Shield), R1.1
/MCU_USB/VBUS_CONN: F1.1, J2.1 (VBUS)
/MCU_USB/VREG_AVDD: C18.1, R5.2, U1.46 (VREG_AVDD)
/MCU_USB/VREG_LX: L1.2, U1.48 (VREG_LX)
/MCU_USB/XIN: C19.1, U1.21 (XIN), Y1.1
/MCU_USB/XOUT: R6.2, U1.22 (XOUT)
/MCU_USB/XTAL_X: C20.1, R6.1, Y1.3
GND: C1.2, C2.2, C3.2, C4.2, C5.2, C6.2, C7.2, C8.2, C9.2, C10.2, C11.2, C12.2, C13.2, C14.2, C15.2, C16.2, C17.2, C18.2, C19.2, C20.2, C21.2, D1.1 (K), D2.1 (K), J2.4 (GND), J3.2, J3.MP (MountPin), R1.2, SW1.2, SW2.2, U1.47 (VREG_PGND), U1.61 (GND), U2.2 (GND), U3.2 (GND), U4.1, U4.4, U4.7 (GND), U4.10, U4.13, Y1.2 (G), Y1.4 (G); also elsewhere on the board
LEDK_LATCH: U4.3; also elsewhere on the board
LEDK_MOSI: U4.8; also elsewhere on the board
LEDK_OEn: U4.11; also elsewhere on the board
LEDK_SCK: U4.6; also elsewhere on the board
MCU_DRDY: U1.15 (GPIO11); also elsewhere on the board
MCU_MISO: U1.7 (GPIO4); also elsewhere on the board
unnamed: D1.2 (A), R10.2
unnamed: D2.2 (A), R9.2
VBUS: C2.1, F1.2, R10.1, U2.1 (VIN), U2.3 (EN), U3.5 (VBUS); also elsewhere on the board

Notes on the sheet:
RN1 pull-ups keep all four opto LEDs off while the MCU is in reset / unprogrammed.
DVDD (1.1 V) decoupling
3V3 decoupling: 100n at IOVDD (x6) / QSPI_IOVDD / USB_OTP_VDD / ADC_AVDD pins + 10u bulk
C16 at VREG_VIN, C17 at L1 output, C18 + R5 filter VREG_AVDD. L1 is polarised: follow the RP2350 datasheet layout.
USB-B input, ESD protection, 3.3 V LDO (USB / PC ground domain)
Opto LED drivers (LED off = isolated line high)
D1: USB power
D2: activity
Core 1.1 V switching regulator (RP2350 reference circuit)
RP2354A (2 MB flash in package)

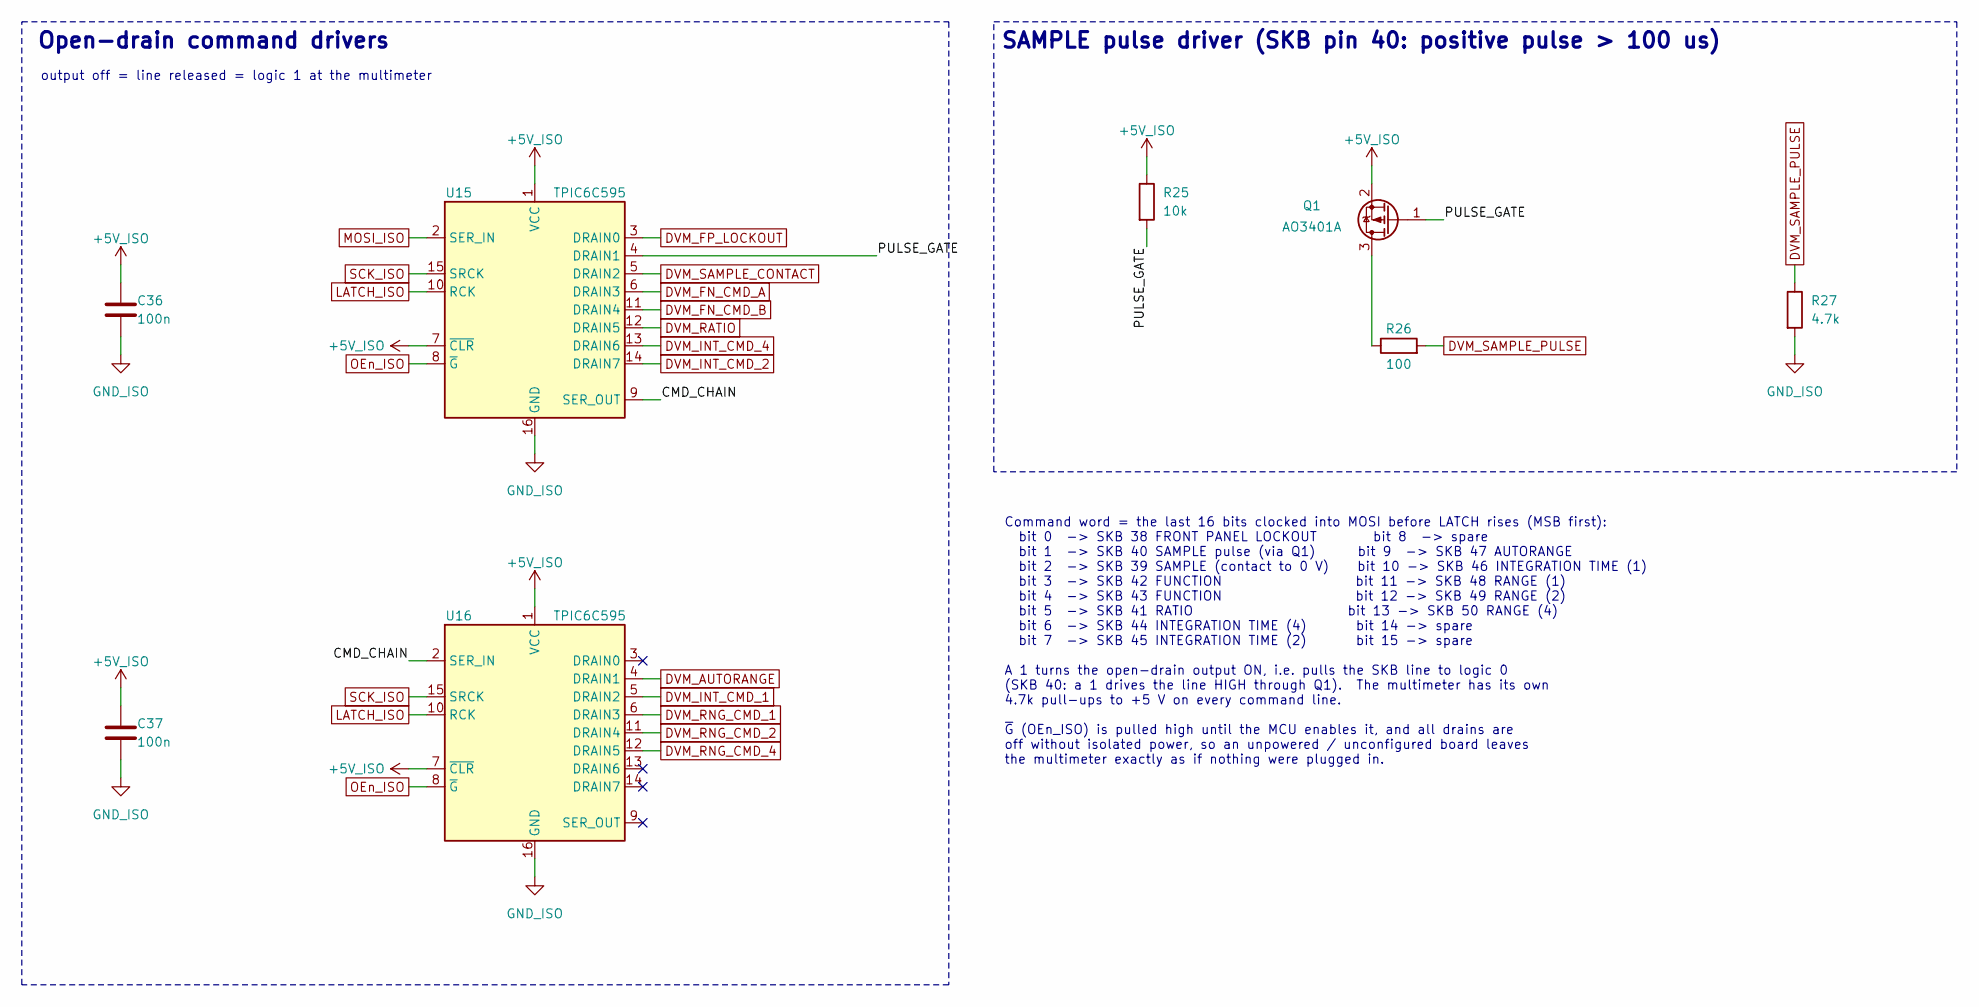
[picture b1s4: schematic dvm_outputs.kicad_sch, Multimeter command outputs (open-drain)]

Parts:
C36, C37: 100n; C_0603_1608Metric; MPN CC0603KRX7R9BB104; LCSC C14663
Q1: AO3401A; SOT-23; MPN AO3401A; LCSC C15127
R25: 10k; R_0603_1608Metric; MPN 0603WAF1002T5E; LCSC C25804
R26: 100; R_0603_1608Metric; MPN 0603WAF1000T5E; LCSC C22775
R27: 4.7k; R_0603_1608Metric; MPN 0603WAF4701T5E; LCSC C23162
U15, U16: TPIC6C595; SOIC-16_3.9x9.9mm_P1.27mm; MPN TPIC6C595DR; LCSC C350572

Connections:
+5V_ISO: C36.1, C37.1, Q1.2 (S), R25.1, U15.1 (VCC), U15.7 (~CLR), U16.1 (VCC), U16.7 (~CLR); also elsewhere on the board
/DVM_OUTPUTS/CMD_CHAIN: U15.9 (SER_OUT), U16.2 (SER_IN)
/DVM_OUTPUTS/PULSE_GATE: Q1.1 (G), R25.2, U15.4 (DRAIN1)
DVM_AUTORANGE: U16.4 (DRAIN1); also elsewhere on the board
DVM_FN_CMD_A: U15.6 (DRAIN3); also elsewhere on the board
DVM_FN_CMD_B: U15.11 (DRAIN4); also elsewhere on the board
DVM_FP_LOCKOUT: U15.3 (DRAIN0); also elsewhere on the board
DVM_INT_CMD_1: U16.5 (DRAIN2); also elsewhere on the board
DVM_INT_CMD_2: U15.14 (DRAIN7); also elsewhere on the board
DVM_INT_CMD_4: U15.13 (DRAIN6); also elsewhere on the board
DVM_RATIO: U15.12 (DRAIN5); also elsewhere on the board
DVM_RNG_CMD_1: U16.6 (DRAIN3); also elsewhere on the board
DVM_RNG_CMD_2: U16.11 (DRAIN4); also elsewhere on the board
DVM_RNG_CMD_4: U16.12 (DRAIN5); also elsewhere on the board
DVM_SAMPLE_CONTACT: U15.5 (DRAIN2); also elsewhere on the board
DVM_SAMPLE_PULSE: R26.2, R27.1; also elsewhere on the board
GND_ISO: C36.2, C37.2, R27.2, U15.16 (GND), U16.16 (GND); also elsewhere on the board
LATCH_ISO: U15.10 (RCK), U16.10 (RCK); also elsewhere on the board
MOSI_ISO: U15.2 (SER_IN); also elsewhere on the board
unnamed: Q1.3 (D), R26.1
OEn_ISO: U15.8 (~G), U16.8 (~G); also elsewhere on the board
SCK_ISO: U15.15 (SRCK), U16.15 (SRCK); also elsewhere on the board

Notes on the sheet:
Open-drain command drivers
SAMPLE pulse driver (SKB pin 40: positive pulse > 100 us)
output off = line released = logic 1 at the multimeter
Command word = the last 16 bits clocked into MOSI before LATCH rises (MSB first): bit 0 -> SKB 38 FRONT PANEL LOCKOUT bit 8 -> spare bit 1 -> SKB 40 SAMPLE pulse (via Q1) bit 9 -> SKB 47 AUTORANGE bit 2 -> SKB 39 SAMPLE (contact to 0 V) bit 10 -> SKB 46 INTEGRATION TIME (1) bit 3 -> SKB 42 FUNCTION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
